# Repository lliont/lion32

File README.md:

# lion32
Lion FPGA CPU/Computer 32bit version

This is the 32bit version of my 16bit Lion System (lliont/lion16 repository).

lionsys.sof and lionsys.jic are the files for configuration of a QMTech Cyclone V FPGA board for Lion32.

32.zip contains files for the 30MB FAT partition on a SDCard for Lion to boot.

Lionasm.exe is an assembler for Lion32. 

Liontiny32.asm is the Basic source file that when compiled and it's output Liontiny.bin is named BOOT.BIN (exists in 32.zip) and copied to sdcard it boots lion32 in tiny basic.

Lion1.sch and Lion1.brd are eagle files for the Lion base board.

Lionc directory contains small-c for Lion files, cc.exe the compiler, Lionlink.exe - llink.exe the linker, clib.bin is the library

Hardware design and software released under the Creative Commons License BY-NC-SA https://creativecommons.org/licenses/by-nc-sa/4.0/

Theodoulos Liontakis.

Project Pages:

https://hackaday.io/project/162876-lion-fpga-cpucomputer

http://users.sch.gr/tliontakis/index.php/my-projects/13-vhdl-cpu

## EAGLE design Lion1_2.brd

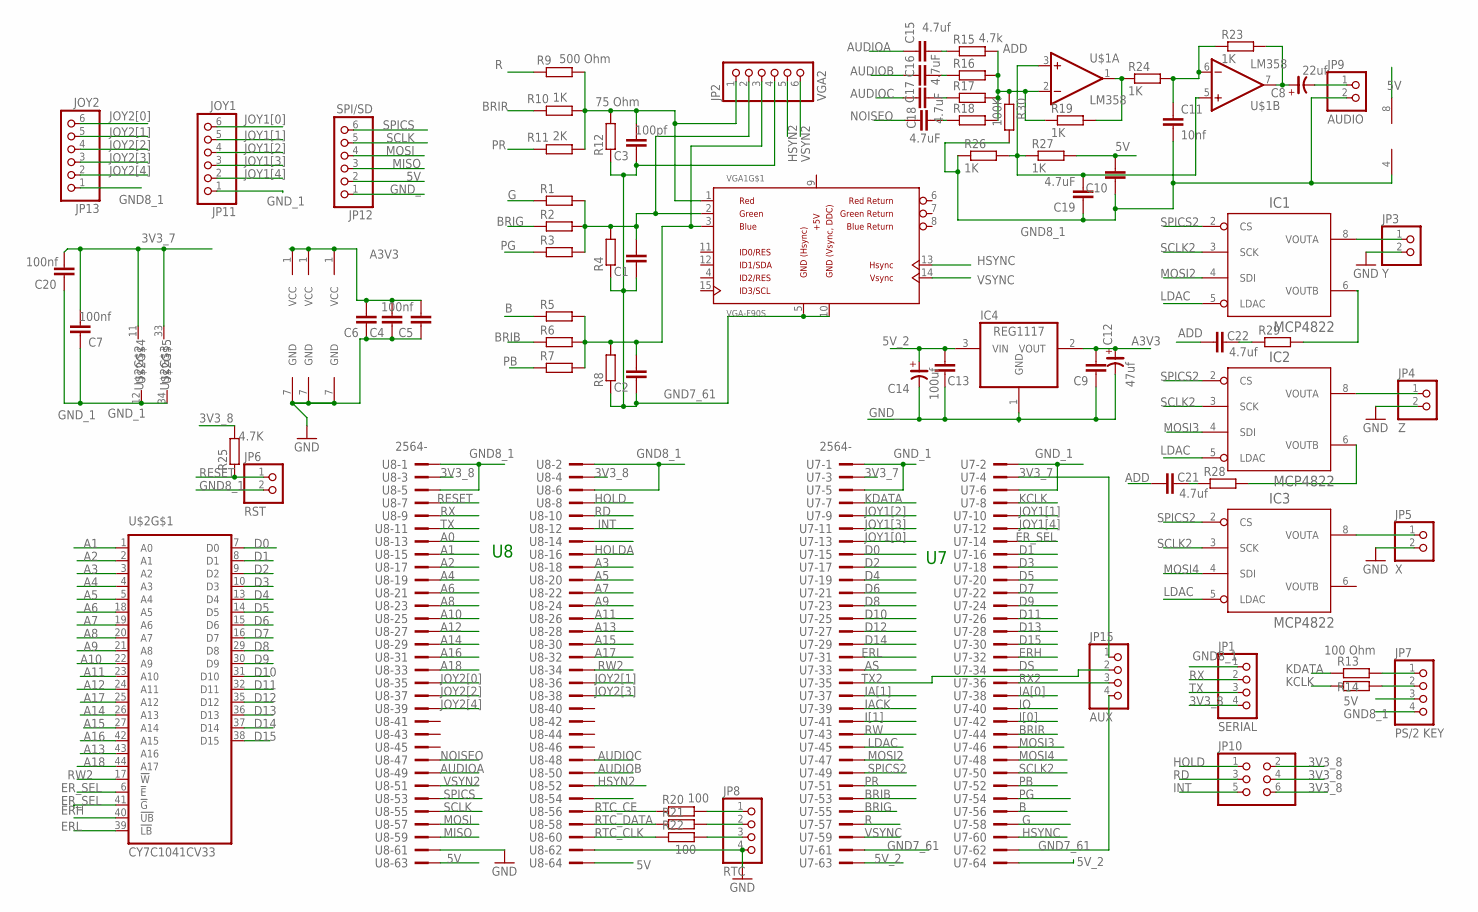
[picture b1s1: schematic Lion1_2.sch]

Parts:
C1, C2, C4, C6, C9, C10, C13: C-EU050-025X075; C050-025X075
C3: 100pf; C050-025X075
C5: 100nf; C050-025X075
C7, C20: 100nf; C0805
C8: 22uf; CE-025X060
C11: 10nf; C050-025X075
C12: 47uf; CE-025X060
C14: 100uf; CE-025X060
C15, C21, C22: 4.7uf; C050-025X075
C16, C17, C18, C19: 4.7uF; C050-025X075
IC1, IC2, IC3: MCP4822; DIL08
IC4: REG1117; SOT223
JP1: SERIAL; 1X04
JP2: VGA2; 1X06
JP3: Y; 1X02
JP4: Z; 1X02
JP5: X; 1X02
JP6: RST; 1X02
JP7: PS/2 KEY; 1X04
JP8: RTC; 1X04
JP9: AUDIO; 1X02
JP10: PINHD-2X3; 2X03
JP11: JOY1; 1X06
JP12: SPI/SD; 1X06
JP13: JOY2; 1X06
JP15: AUX; 1X04
R1, R2, R3, R4, R5, R6, R7, R8, R14, R22: R-EU_0204/7; 0204/7
R9: 500 Ohm; 0204/7
R10, R19, R23, R24, R26, R27: 1K; 0204/7
R11: 2K; 0204/7
R12: 75 Ohm; 0204/7
R13: 100 Ohm; 0204/7
R15: 4.7k; 0204V
R16, R17, R18, R28, R29: R-EU_0204/2V; 0204V
R20, R21: 100; 0204/7
R25: 4.7K; 0204/5
R30: 100K; 0204/7
U7, U8: 2564-; PAK100/2500-64
U$1: LM358; DIL8
U$2: CY7C1041CV33; TSOP44-II
VGA1: VGA-F90S; DB-15-F90+SHIELD-SMALL_PADS

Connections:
3V3_7: C7.2, C20.2, JP15.1, U7.3, U7.4, U$2.11 (VCC), U$2.33 (VCC)
3V3_8: JP1.4, JP10.2, JP10.4, JP10.6, R25.2, U8.3, U8.4
5V: C10.2, JP7.3, JP12.2, R27.2, U8.63, U8.64, U$1.8 (V+)
5V_2: C13.2, C14.+, IC4.3 (VIN), U7.63, U7.64
+5V: VGA1.9 (+5V)
A0: U8.13
A1: U8.15, U$2.1 (A0)
A2: U8.17, U$2.2 (A1)
A3: U8.18, U$2.3 (A2)
A3V3: C4.2, C5.2, C6.2, C9.2, C12.+, IC1.1 (VCC), IC2.1 (VCC), IC3.1 (VCC), IC4.2 (VOUT)
A4: U8.19, U$2.4 (A3)
A5: U8.20, U$2.5 (A4)
A6: U8.21, U$2.18 (A5)
A7: U8.22, U$2.19 (A6)
A8: U8.23, U$2.20 (A7)
A9: U8.24, U$2.21 (A8)
A10: U8.25, U$2.22 (A9)
A11: U8.26, U$2.23 (A10)
A12: U8.27, U$2.24 (A11)
A13: U8.28, U$2.43 (A16)
A14: U8.29, U$2.26 (A13)
A15: U8.30, U$2.27 (A14)
A16: U8.31, U$2.42 (A15)
A17: U8.32, U$2.25 (A12)
A18: U8.33, U$2.44 (A17)
ADD: C21.1, C22.1, R15.2, R16.2, R17.2, R18.2, R19.1, R30.1, U$1.2 (-IN)
AS: U7.33
AUDIOA: C15.1, U8.49
AUDIOB: C16.1, U8.50
AUDIOC: C17.1, U8.48
B: R5.1, U7.56
BRIB: R6.1, U7.53
BRIG: R2.1, U7.55
BRIR: R10.1, U7.44
D0: U7.15, U$2.7 (D0)
D1: U7.16, U$2.8 (D1)
D2: U7.17, U$2.9 (D2)
D3: U7.18, U$2.10 (D3)
D4: U7.19, U$2.13 (D4)
D5: U7.20, U$2.14 (D5)
D6: U7.21, U$2.15 (D6)
D7: U7.22, U$2.16 (D7)
D8: U7.23, U$2.29 (D8)
D9: U7.24, U$2.30 (D9)
D10: U7.25, U$2.31 (D10)
D11: U7.26, U$2.32 (D11)
D12: U7.27, U$2.35 (D12)
D13: U7.28, U$2.36 (D13)
D14: U7.29, U$2.37 (D14)
D15: U7.30, U$2.38 (D15)
DS: U7.34
ERH: U7.32, U$2.40 (!UB)
ERL: U7.31, U$2.39 (!LB)
ER_SEL: U7.14, U$2.6 (!E), U$2.41 (!G)
G: R1.1, U7.58
GND7_61: C1.1, C2.1, C3.1, JP2.4, JP15.4, R4.1, R8.1, R12.1, U7.61, U7.62, VGA1.5 (GND), VGA1.10 (GND)
GND8_1: C10.1, C11.2, C19.1, JP1.1, JP6.2, JP7.4, JP9.2, JP13.1, R26.1, R30.2, U8.1, U8.2, U8.5, U8.6, U$1.4 (V-)
GND_: C4.1, C5.1, C6.1, C9.1, C12.-, C13.1, C14.-, IC1.7 (GND), IC2.7 (GND), IC3.7 (GND), IC4.1 (GND), JP3.2, JP4.2, JP5.2, JP8.4, JP12.1, U8.61, U8.62
GND_1: C7.1, C20.1, JP11.1, U7.1, U7.2, U7.5, U7.6, U$2.12 (VSS), U$2.34 (VSS)
HOLD: JP10.1, U8.8
HOLDA: U8.16
HSYN2: JP2.5, U8.52
HSYNC: U7.60, VGA1.13 (VGA-HSYNC)
IACK: U7.39
IA[0]: U7.38
IA[1]: U7.37
INT: JP10.5, U8.12
IO: U7.40
I[0]: U7.42
I[1]: U7.41
JOY1[0]: JP11.6, U7.13
JOY1[1]: JP11.5, U7.10
JOY1[2]: JP11.4, U7.9
JOY1[3]: JP11.3, U7.11
JOY1[4]: JP11.2, U7.12
JOY2[0]: JP13.6, U8.35
JOY2[1]: JP13.5, U8.36
JOY2[2]: JP13.4, U8.37
JOY2[3]: JP13.3, U8.38
JOY2[4]: JP13.2, U8.39
KCLK: R14.1, U7.8
KDATA: R13.1, U7.7
LDAC: IC1.5 (LDAC), IC2.5 (LDAC), IC3.5 (LDAC), U7.45
MISO: JP12.3, U8.59
MOSI: JP12.4, U8.57
MOSI2: IC1.4 (SDI), U7.47
MOSI3: IC2.4 (SDI), U7.46
MOSI4: IC3.4 (SDI), U7.48
unnamed: C1.2, JP2.2, R1.2, R2.2, R3.2, R4.2, VGA1.2 (VGA-G)
unnamed: IC2.6 (VOUTB), R28.2
unnamed: C19.2, R26.2, R27.1, U$1.3 (+IN), U$1.5 (+IN)
unnamed: C15.2, R15.1
unnamed: IC3.8 (VOUTA), JP5.1
unnamed: C2.2, JP2.3, R5.2, R6.2, R7.2, R8.2, VGA1.3 (VGA-B)
unnamed: IC2.8 (VOUTA), JP4.1
unnamed: IC1.8 (VOUTA), JP3.1
unnamed: C21.2, R28.1
unnamed: C3.2, JP2.1, R9.2, R10.2, R11.2, R12.2, VGA1.1 (VGA-R)
unnamed: R19.2, R24.1, U$1.1 (OUT)
unnamed: JP7.1, R13.2
unnamed: JP7.2, R14.2
unnamed: C8.-, JP9.1
unnamed: JP8.1, R20.2
unnamed: JP8.2, R21.2
unnamed: JP8.3, R22.2
unnamed: C8.+, R23.2, U$1.7 (OUT)
unnamed: C11.1, R23.1, R24.2, U$1.6 (-IN)
unnamed: C16.2, R16.1
unnamed: C17.2, R17.1
unnamed: C18.2, R18.1
unnamed: C22.2, R29.1
unnamed: IC1.6 (VOUTB), R29.2
NOISEO: C18.1, U8.47
PB: R7.1, U7.52
PG: R3.1, U7.54
PR: R11.1, U7.51
R: R9.1, U7.57
RD: JP10.3, U8.10
RESET: JP6.1, R25.1, U8.7
RTC_CE: R20.1, U8.56
RTC_CLK: R22.1, U8.60
RTC_DATA: R21.1, U8.58
RW: U7.43
RW2: U8.34, U$2.17 (!W)
RX: JP1.2, U8.9
RX2: JP15.3, U7.36
SCLK: JP12.5, U8.55
SCLK2: IC1.3 (SCK), IC2.3 (SCK), IC3.3 (SCK), U7.50
SPICS: JP12.6, U8.53
SPICS2: IC1.2 (CS), IC2.2 (CS), IC3.2 (CS), U7.49
TX: JP1.3, U8.11
TX2: JP15.2, U7.35
VSYN2: JP2.6, U8.51
VSYNC: U7.59, VGA1.14 (VGA-VSYNC)

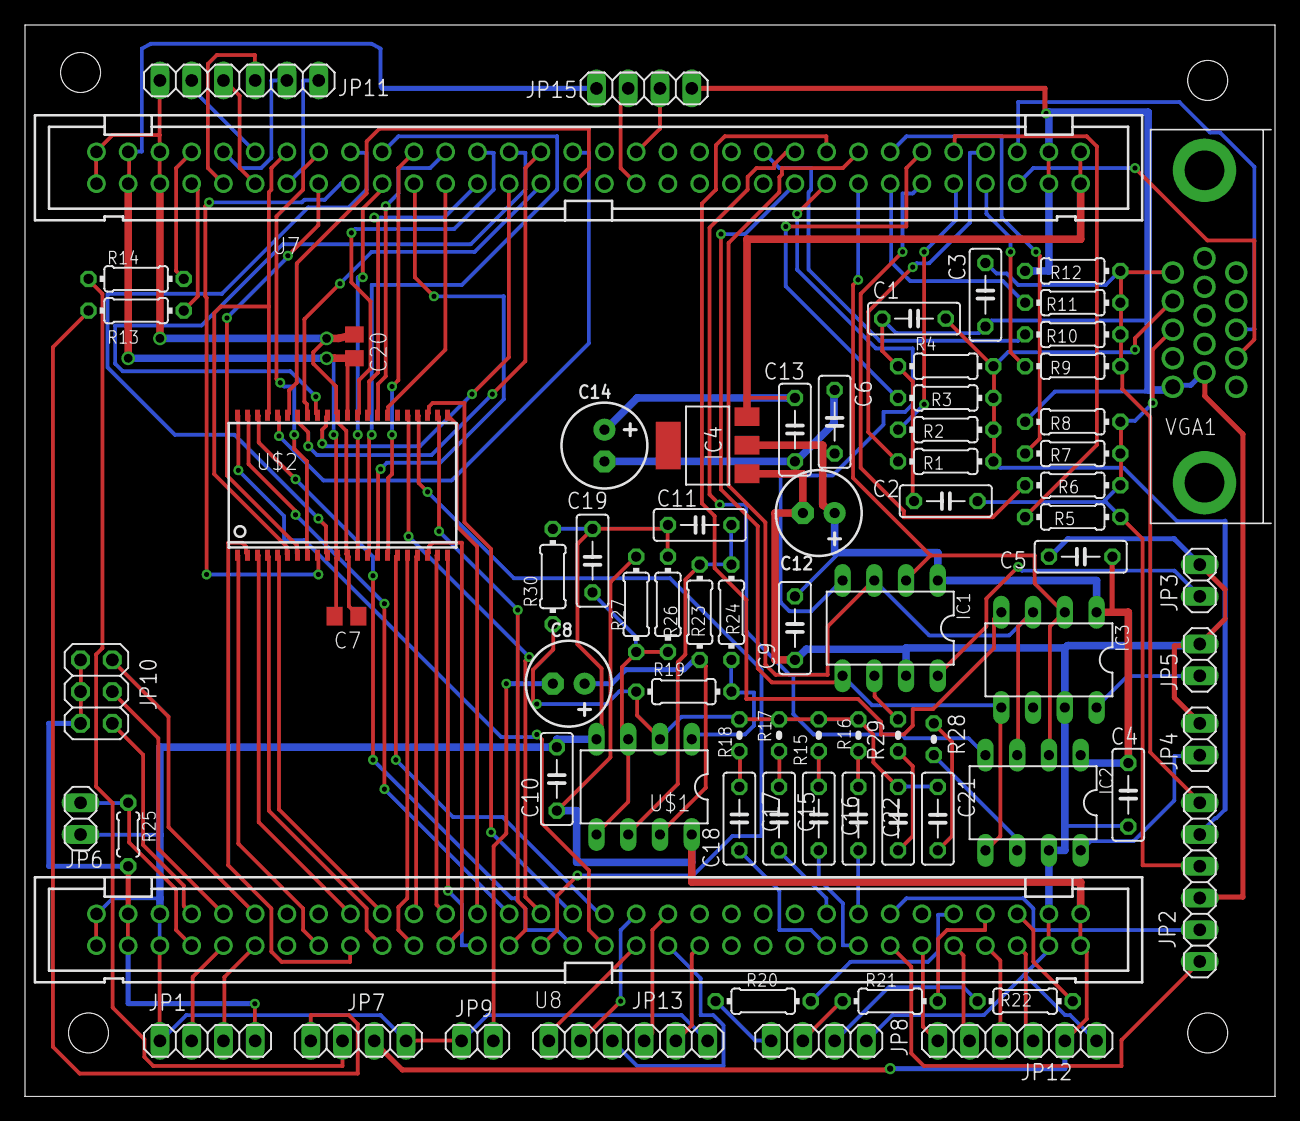
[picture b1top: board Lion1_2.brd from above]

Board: 2 copper layers, 100.0 x 85.7 mm, 75 parts (0 on the bottom side), 122 nets.

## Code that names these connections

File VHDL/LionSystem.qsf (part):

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set_location_assignment PIN_B16 -to HSYN
set_location_assignment PIN_C16 -to VSYN
set_location_assignment PIN_V18 -to Reset
set_location_assignment PIN_AA13 -to HOLD
set_location_assignment PIN_AB15 -to RD
set_location_assignment PIN_M16 -to MISO
set_location_assignment PIN_K22 -to MOSI
set_location_assignment PIN_L17 -to SCLK
set_location_assignment PIN_M22 -to SPICS
set_location_assignment PIN_AA15 -to Rx
set_location_assignment PIN_Y15 -to Tx
set_global_assignment -name RESERVE_DCLK_AFTER_CONFIGURATION "USE AS PROGRAMMING PIN"
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set_global_assignment -name STRATIXV_CONFIGURATION_SCHEME "PASSIVE SERIAL"
set_global_assignment -name OUTPUT_IO_TIMING_ENDPOINT "NEAR END"
set_global_assignment -name ACTIVE_SERIAL_CLOCK FREQ_100MHZ
set_location_assignment PIN_L18 -to VSYN2
set_location_assignment PIN_L19 -to HSYN2
set_location_assignment PIN_N19 -to AUDIOB
set_location_assignment PIN_AA1 -to KCLK
set_location_assignment PIN_AA2 -to KDATA
set_location_assignment PIN_N16 -to RTC_CLK
set_location_assignment PIN_K21 -to RTC_DATA
set_location_assignment PIN_K17 -to RTC_CE
set_location_assignment PIN_N1 -to JOYST1[0]
set_location_assignment PIN_W2 -to JOYST1[1]
set_location_assignment PIN_Y3 -to JOYST1[2]
set_location_assignment PIN_U1 -to JOYST1[3]
set_location_assignment PIN_U2 -to JOYST1[4]
set_location_assignment PIN_M21 -to NOISEO
set_location_assignment PIN_M18 -to AUDIOA
set_location_assignment PIN_M20 -to AUDIOC
set_location_assignment PIN_A13 -to PG
set_location_assignment PIN_D13 -to PR
set_location_assignment PIN_C13 -to PB
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set_location_assignment PIN_C9 -to Iv[0]
set_location_assignment PIN_G10 -to RWo
set_global_assignment -name OPTIMIZE_SSN OFF
set_location_assignment PIN_E12 -to SPICS2
set_location_assignment PIN_D12 -to SCLK2
set_location_assignment PIN_B12 -to MOSI2
set_location_assignment PIN_C11 -to LDAC
set_global_assignment -name PLACEMENT_EFFORT_MULTIPLIER 1.275
set_global_assignment -name OPTIMIZATION_TECHNIQUE BALANCED
set_global_assignment -name SYNCHRONIZER_IDENTIFICATION AUTO
set_global_assignment -name OPTIMIZE_IOC_REGISTER_PLACEMENT_FOR_TIMING NORMAL
set_global_assignment -name PHYSICAL_SYNTHESIS_EFFORT EXTRA
set_location_assignment PIN_B11 -to MOSI3
set_global_assignment -name INFER_RAMS_FROM_RAW_LOGIC OFF
set_global_assignment -name AUTO_RAM_RECOGNITION ON
set_location_assignment PIN_A12 -to MOSI4
set_global_assignment -name PARTITION_NETLIST_TYPE SOURCE -section_id Top
set_global_assignment -name PARTITION_FITTER_PRESERVATION_LEVEL PLACEMENT_AND_ROUTING -section_id Top
set_global_assignment -name PARTITION_COLOR 16764057 -section_id Top
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set_location_assignment PIN_G1 -to D[2]
set_location_assignment PIN_L2 -to D[1]
set_location_assignment PIN_L1 -to D[0]
set_location_assignment PIN_B13 -to BRIB
set_location_assignment PIN_A15 -to BRIG
set_location_assignment PIN_F10 -to BRIR
set_location_assignment PIN_N2 -to ER_SEL
set_location_assignment PIN_D9 -to ERH
set_location_assignment PIN_E9 -to ERL
set_location_assignment PIN_W19 -to RWo2
set_global_assignment -name SEED 1
set_global_assignment -name ROUTER_TIMING_OPTIMIZATION_LEVEL NORMAL
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
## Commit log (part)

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2021-01-05 First Upload
2021-01-05 Eagle files for Lion32 base board
2021-01-05 inital upload
2021-01-05 Fixed
2021-01-06 Sound volume fix
2021-01-10 Cursor, editing
2021-01-11 java optimization, cmd line edit
2021-01-11 edit command
2021-01-12 more edit
2021-01-12 small improvements
2021-02-17 256 colours, 2 digital audio channels, 56 sprites
2021-02-24 Fix java cos,sin, floating divide and more
2021-02-25 timer bug fixed
2021-03-01 Vhdl source
2021-03-04 ALNG command + optimizations
2021-03-06 MOD bug
2021-03-24 New cpu instructions, file extensions, PCM fix
2021-03-25 dir file size align
2021-04-19 few new cpu instructions, new interrupt to allocate memory
2021-04-19 reserve memory for rom routines, TB bug fix
2021-04-21 basic memory
2021-06-01 Small-C files
2021-06-04 file write routines
2021-06-05 command line assembler
2021-11-30 some syslib functions, audio sample play command, 1 resistor added
2021-12-04 Added functions in syslib c library
2021-12-04 more functions
2021-12-06 something
2021-12-06 user defined characters above ASCII 127 table at 19008 (1K)
2021-12-14 more functions in syslib, new scroll routine variants
2021-12-16 floating point library
2022-01-18 Bug fix
2022-01-24 New operations SRL.D Reg,Reg SRL.D Reg,Reg Integer division optimization
2022-04-02 Faster relative instructions, changed noise channel
2022-05-05 New operations, c float lib bugs fix, ....
2023-01-08 Documentation
2023-01-08 lcc-llcasm compiler
2023-01-14 some new operations
2023-01-14 updated sdcard files
2023-11-12 more reliabile spi

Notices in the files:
VHDL/LionSystem.qsf:
Copyright (C) 1991-2012 Altera Corporation
parts and their libraries:
eagle-6.5.0-atari: Copyright (c) 2010
Copyright (c) 2009
This library is licensed under the
Creative Commons Attribution 3.0 United States License.
rc-master: Copyright (C) 2007, Bob Starr
